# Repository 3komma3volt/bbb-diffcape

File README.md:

# bbb-diffcape

A simple Beaglebone black cape for controlling LED pixels with differential signals

# Usage
It consists of a simple cape with 8 diffential (RS422) outputs to control pixel strings (e.g. with WS2812B LEDs) over long distances. 
The project includes a receiver board to generate single-ended data for the pixels
It is compatible with [FPP Falcon Player](https://github.com/FalconChristmas/fpp) 
The manufacturing files include LCSC component numbers for direct ordering at [JLCPCB](https://jlcpcb.com)
Only the direct-solder fuse, the headers and the screw terminals have to be soldered manually, if ordered at JLCPCB.

> The boards have very simple designs. 2 layer, no impedance matching, only a bit ESD protection, no supply protection!

## Sending Cape

The folder **bbb-diffcape** contains the [KICAD](https://www.kicad.org) schematic, board and Gerber files. 

> Be aware that the Gerbers and board file are not consistent! In the  Gerbers, the screw terminals are a bit too narrow to each other. It works, but the plugged in connectors have to be bend a bit. The KICAD board is already corrected in R2.

 -  A 0.96" I2C OLED TFT can be mounted, which is supported by FPP to get some status information.
 - 5V connector supplies the Beaglebone and the Diffcape
 - Copy the BBB-Diff.json to the */opt/fpp/capes/bbb/strings* folder for correct configuration within FPP

# bbb-diffcape

A simple Beaglebone black cape for controlling LED pixels with differential signals

# Usage
It consists of a simple cape with 8 diffential (RS422) outputs to control pixel strings (e.g. with WS2812B LEDs) over long distances. 
The project includes a receiver board to generate single-ended data for the pixels
It is compatible with [FPP Falcon Player](https://github.com/FalconChristmas/fpp) 
The manufacturing files include LCSC component numbers for direct ordering at [JLCPCB](https://jlcpcb.com)
Only the direct-solder fuse, the headers and the screw terminals have to be soldered manually, if ordered at JLCPCB.

> The boards have very simple designs. 2 layer, no impedance matching, only a bit ESD protection, no supply protection!

## Sending Cape

The folder **bbb-diffcape** contains the [KICAD](https://www.kicad.org) schematic, board and Gerber files. 

> Be aware that the Gerbers and board file are not consistent! In the  Gerbers, the screw terminals are a bit too narrow to each other. It works, but the plugged in connectors have to be bend a bit. The KICAD board is already corrected in R2.

 -  A 0.96" I2C OLED TFT can be mounted, which is supported by FPP to get some status information.
 - 5V connector supplies the Beaglebone and the Diffcape
 - Copy the BBB-Diff.json to the */opt/fpp/capes/bbb/strings* folder for correct configuration within FPP

> This board is tested and fully functional on all channels!

## Receiver

The receiver is designed to support two supply variants

 - Supply with 5V: Just connect power and data as in the picture and the pixel string
 - Supply with 24V via RJ45: For easier cableing, a RJ45 connector for data and power. So there has to be a 24V power supply on the transmission side which powers the system. On the receiver side, a DC/DC converter is needed to power down to 5V. 
 - Excellent for per-prop-use. So one receiver per prop can be used with simple RJ45 cabelling (22AWG) with ~25W supply @ 10m without a big voltage drop
 - Folder "mechanical" contains a FreeCAD file for a simple hotglue mount
 
Because there is no voltage regulator, the receiver is not suited for use with 12V pixels without modifications!

> This board is tested and fully functional!

## ReceiverTransmitter

Receiver with integrated transmitter. With this PCB, you can go back from the last pixel's output to the board and regenerate differential data. It also forwards the 24V power via the RJ45 connector.

> This board is tested and fully functional!

## Distributor

With the distributor power and data can be transfered with standard patch cords. A 3A 5V DC/DC converter is used to supply the beaglebone black

> This board is untested!

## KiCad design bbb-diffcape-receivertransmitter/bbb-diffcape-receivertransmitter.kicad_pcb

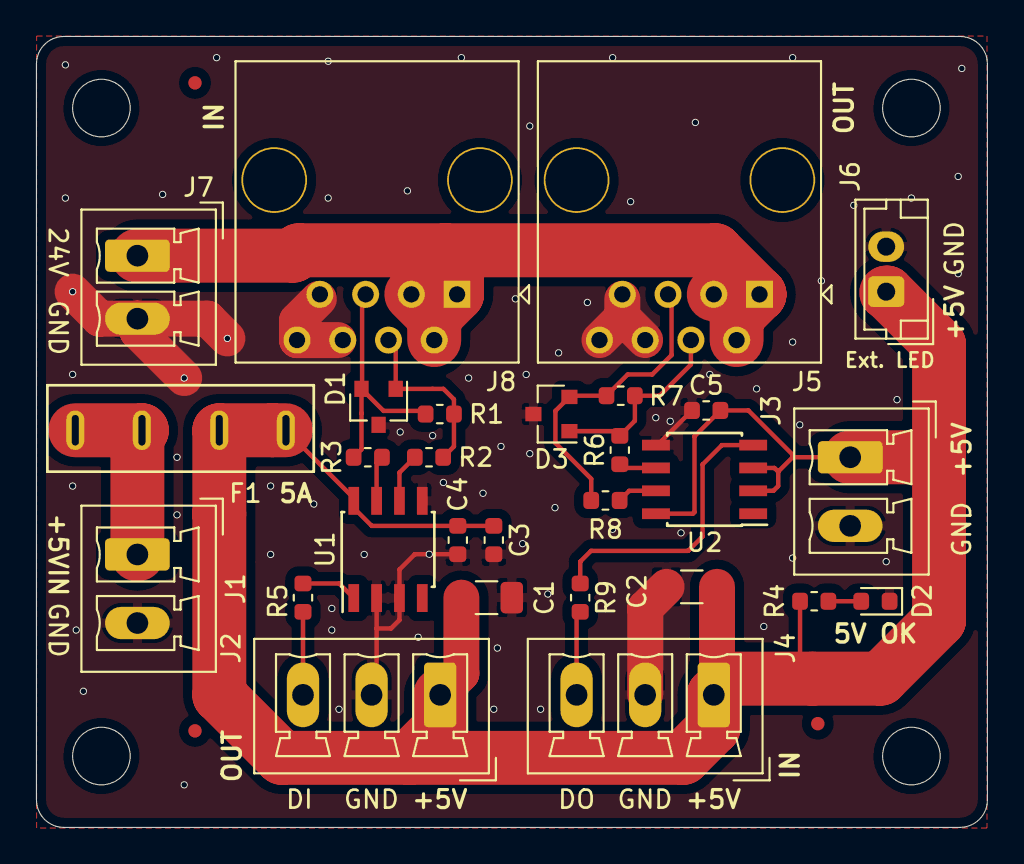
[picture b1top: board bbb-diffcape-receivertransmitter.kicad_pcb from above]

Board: 2 copper layers, 52.8 x 43.9 mm, 35 parts (0 on the bottom side), 17 nets.

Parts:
C1, C2: 100u; C_1206_3216Metric
C3, C4, C5: 100n; C_0603_1608Metric
D1, D3: PSM712; SOT-23
D2: LED; LED_0603_1608Metric
F1: 5A; TLZWLA-Minifuse
FID1, FID2, FID3: Fiducial; Fiducial_0.75mm_Mask1.5mm
H1, H2, H3, H4: MountingHole; MountingHole_3.2mm_M3
J1, J3: Screw_Terminal_01x02; PhoenixContact_MCV_1,5_2-G-3.81_1x02_P3.81mm_Vertical
J2, J4: Screw_Terminal_01x03; PhoenixContact_MCV_1,5_3-G-3.81_1x03_P3.81mm_Vertical
J5, J8: RJ45; RJ45_OST_PJ012-8P8CX_Vertical
J6: Conn_01x02_Male; JST_EH_B2B-EH-A_1x02_P2.50mm_Vertical
J7: Screw_Terminal_01x02; PhoenixContact_MCV_1,5_2-G-3.5_1x02_P3.50mm_Vertical
R1, R7: 120; R_0603_1608Metric
R2, R3, R5, R6, R8, R9: 10; R_0603_1608Metric
R4: 470; R_0603_1608Metric
U1, U2: SP3485EN; SOIC-8_3.9x4.9mm_P1.27mm

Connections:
+5V: C1.1, C2.1, C3.1, C4.1, C5.1, F1.1, J2.1, J3.1, J4.1, J6.1, R4.2, U1.8, U2.2, U2.3, U2.8
+24V: J5.1, J5.2, J5.3, J7.1, J8.1, J8.2, J8.3
/DataIn: J4.3, R9.2
/PW_In: F1.2, J1.1
/RS422_A: D1.1, J8.4, R1.1, R2.1
/RS422_A_Out: D3.1, J5.4, R6.1, R7.1
/RS422_B: D1.2, J8.5, R1.2, R3.1
/RS422_B_Out: D3.2, J5.5, R7.2, R8.1
GNDD: C1.2, C2.2, C3.2, C4.2, C5.2, D1.3, D2.1, D3.3, J1.2, J2.2, J3.2, J4.2, J5.6, J5.7, J5.8, J6.2, J7.2, J8.6, J8.7, J8.8, U1.2, U1.3, U1.5, U2.5
unnamed: D2.2, R4.1
unnamed: J2.3, R5.2
unnamed: R2.2, U1.6
unnamed: R3.2, U1.7
unnamed: R5.1, U1.1
unnamed: R6.2, U2.6
unnamed: R8.2, U2.7
unnamed: R9.1, U2.4

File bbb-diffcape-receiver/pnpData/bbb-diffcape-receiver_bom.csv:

Comment,Designator,Footprint,LCSC
"100u","C1,C2","Capacitor_SMD:C_1206_3216Metric","C15008"
"100n","C3,C4","Capacitor_SMD:C_0603_1608Metric","C14663"
"PSM712","D1","Package_TO_SOT_SMD:SOT-23","C32677"
"LED","D2","LED_SMD:LED_0603_1608Metric","C72038"
"5A","F1","Fuse:Fuse_Blade_Mini_directSolder",""
"Fiducial","FID1,FID2,FID3","Fiducial:Fiducial_0.75mm_Mask1.5mm",""
"MountingHole","H1,H2,H3,H4","MountingHole:MountingHole_3.2mm_M3",""
"Screw_Terminal_01x03","J2,J5","Connector_Phoenix_MC:PhoenixContact_MCV_1,5_3-G-3.5_1x03_P3.50mm_Vertical",""
"Screw_Terminal_01x02","J1,J3,J4,J7","Connector_Phoenix_MC:PhoenixContact_MCV_1,5_2-G-3.5_1x02_P3.50mm_Vertical",""
"Conn_01x02_Male","J6","Connector_JST:JST_EH_B2B-EH-A_1x02_P2.50mm_Vertical",""
"RJ45","J8","Connector_RJ:RJ45_OST_PJ012-8P8CX_Vertical",""
"120","R1","Resistor_SMD:R_0603_1608Metric","C22787"
"10","R2,R3,R5","Resistor_SMD:R_0603_1608Metric","C22859"
"470","R4","Resistor_SMD:R_0603_1608Metric","C23182"
"SP3485EN","U1","Package_SO:SOIC-8_3.9x4.9mm_P1.27mm",""

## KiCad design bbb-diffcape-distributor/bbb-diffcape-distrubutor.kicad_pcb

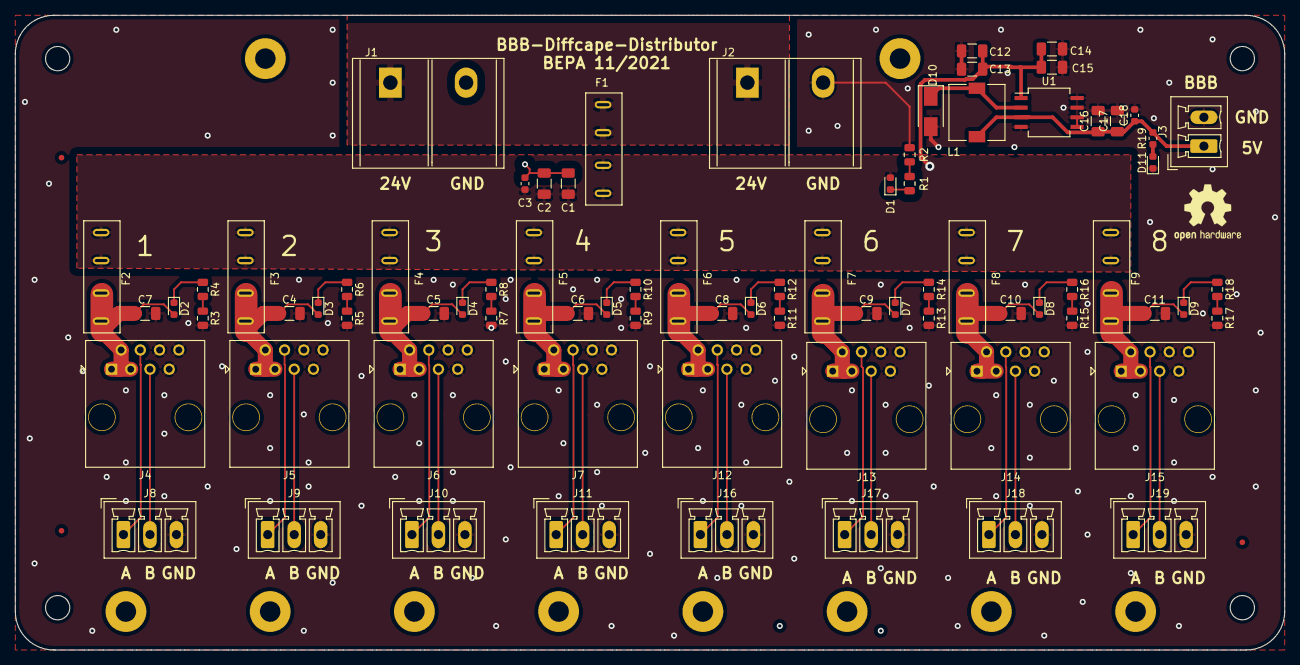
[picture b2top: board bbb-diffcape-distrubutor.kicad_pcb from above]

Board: 2 copper layers, 167.6 x 83.8 mm, 85 parts (0 on the bottom side), 48 nets.

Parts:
C1, C2, C4, C5, C6, C7, C8, C9, C10, C11, C12, C13, C14, C15, C16, C17: 100u; C_1206_3216Metric
C3, C18: 100n; C_0603_1608Metric
D1, D2, D3, D4, D5, D6, D7, D8, D9, D11: LED; LED_0603_1608Metric
D10: SS54; D_SMA
F1: 20A; TLZWLA-Minifuse
F2, F3, F4, F5, F6, F7, F8, F9: 2A; TLZWLA-Minifuse
FID1, FID2, FID3: Fiducial; Fiducial_0.75mm_Mask1.5mm
H1, H2, H3, H4: MountingHole; MountingHole_3.2mm_M3
J1, J2: Screw_Terminal_01x02; KF1000-2P
J3: Screw_Terminal_01x02; PhoenixContact_MCV_1,5_2-G-3.81_1x02_P3.81mm_Vertical
J4, J5, J6, J7, J12, J13, J14, J15: RJ45; RJ45_OST_PJ012-8P8CX_Vertical
J8, J9, J10, J11, J16, J17, J18, J19: Screw_Terminal_01x03; PhoenixContact_MCV_1,5_3-G-3.5_1x03_P3.50mm_Vertical
L1: 68uH; L_7.3x7.3_H3.5
R1, R2, R3, R4, R5, R6, R7, R8, R9, R10, R11, R12, R13, R14, R15, R16, R17, R18: 1k2; R_0805_2012Metric
R19: 470; R_0603_1608Metric
U1: XL1509-5.0E1; SO-8_5.3x6.2mm_P1.27mm

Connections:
+5V: C16.1, C17.1, C18.1, J3.1, L1.2, R19.2, U1.3
+24V: C1.1, C2.1, C3.1, C12.1, C13.1, C14.1, C15.1, D1.2, F1.1, F2.2, F3.2, F4.2, F5.2, F6.2, F7.2, F8.2, F9.2, U1.1
/PW_In: F1.2, J1.1, J2.1
GNDD: C1.2, C2.2, C3.2, C4.2, C5.2, C6.2, C7.2, C8.2, C9.2, C10.2, C11.2, C12.2, C13.2, C14.2, C15.2, C16.2, C17.2, C18.2, D10.2, D11.1, J1.2, J2.2, J3.2, J4.6, J4.7, J4.8, J5.6, J5.7, J5.8, J6.6, J6.7, J6.8, J7.6, J7.7, J7.8, J8.3, J9.3, J10.3, J11.3, J12.6, J12.7, J12.8, J13.6, J13.7, J13.8, J14.6, J14.7, J14.8, J15.6, J15.7, J15.8, J16.3, J17.3, J18.3, J19.3, R2.2, R3.2, R5.2, R7.2, R9.2, R11.2, R13.2, R15.2, R17.2, U1.4, U1.5, U1.6, U1.7, U1.8
unnamed: C4.1, D3.2, F3.1, J5.1, J5.2, J5.3
unnamed: C5.1, D4.2, F4.1, J6.1, J6.2, J6.3
unnamed: C6.1, D5.2, F5.1, J7.1, J7.2, J7.3
unnamed: C7.1, D2.2, F2.1, J4.1, J4.2, J4.3
unnamed: C8.1, D6.2, F6.1, J12.1, J12.2, J12.3
unnamed: C9.1, D7.2, F7.1, J13.1, J13.2, J13.3
unnamed: C10.1, D8.2, F8.1, J14.1, J14.2, J14.3
unnamed: C11.1, D9.2, F9.1, J15.1, J15.2, J15.3
unnamed: D1.1, R1.1
unnamed: D2.1, R4.1
unnamed: D3.1, R6.1
unnamed: D4.1, R8.1
unnamed: D5.1, R10.1
unnamed: D6.1, R12.1
unnamed: D7.1, R14.1
unnamed: D8.1, R16.1
unnamed: D9.1, R18.1
unnamed: D10.1, L1.1, U1.2
unnamed: D11.2, R19.1
unnamed: J4.4, J8.1
unnamed: J4.5, J8.2
unnamed: J5.4, J9.1
unnamed: J5.5, J9.2
unnamed: J6.4, J10.1
unnamed: J6.5, J10.2
unnamed: J7.4, J11.1
unnamed: J7.5, J11.2
unnamed: J12.4, J16.1
unnamed: J12.5, J16.2
unnamed: J13.4, J17.1
unnamed: J13.5, J17.2
unnamed: J14.4, J18.1
unnamed: J14.5, J18.2
unnamed: J15.4, J19.1
unnamed: J15.5, J19.2
unnamed: R1.2, R2.1
unnamed: R3.1, R4.2
unnamed: R5.1, R6.2
unnamed: R7.1, R8.2
unnamed: R9.1, R10.2
unnamed: R11.1, R12.2
unnamed: R13.1, R14.2
unnamed: R15.1, R16.2
unnamed: R17.1, R18.2

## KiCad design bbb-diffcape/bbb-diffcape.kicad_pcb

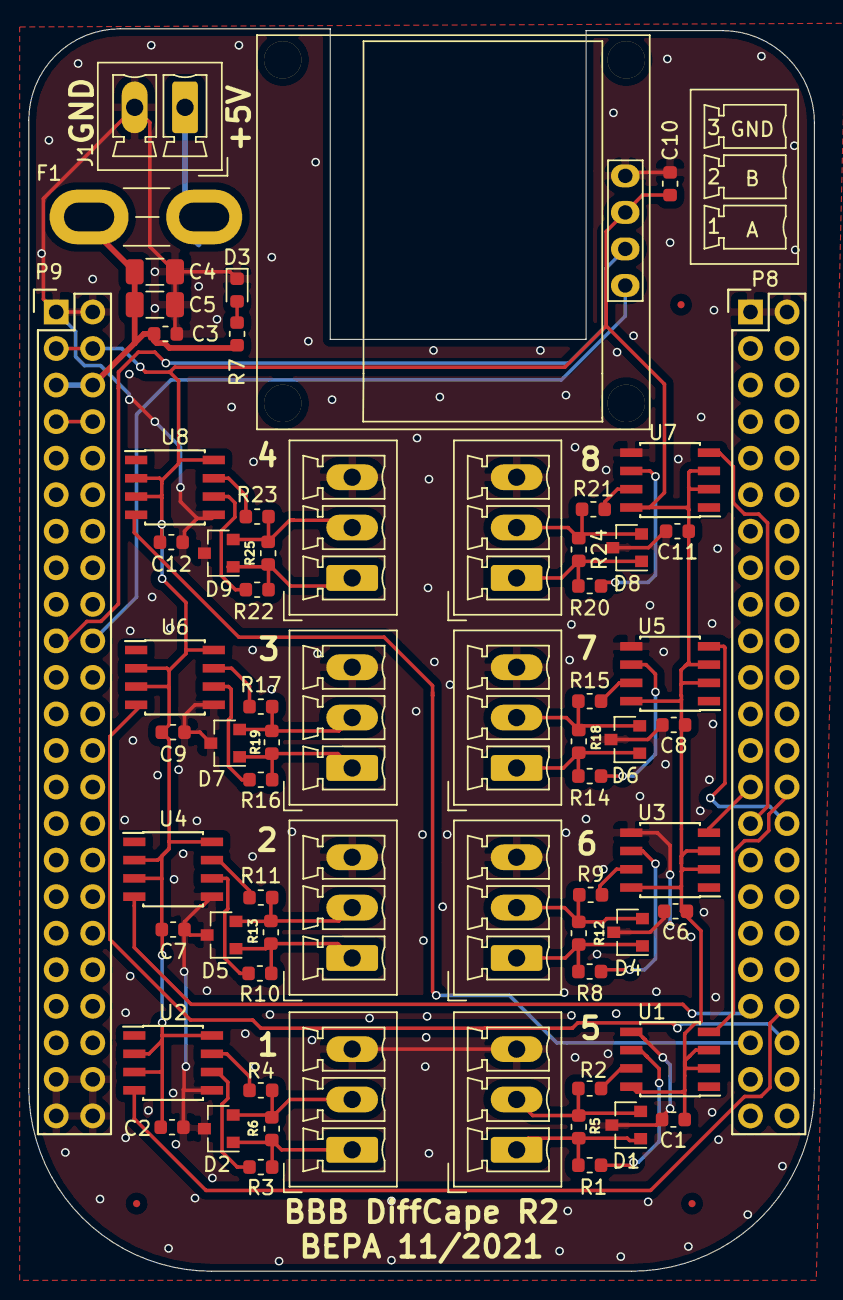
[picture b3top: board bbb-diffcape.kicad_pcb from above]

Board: 2 copper layers, 54.6 x 86.4 mm, 70 parts (0 on the bottom side), 48 nets.

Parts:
Brd1: SSD1306; 128x64OLED
C1, C2, C3, C6, C7, C8, C9, C10, C11, C12: 100n; C_0603_1608Metric
C4, C5: 100u; C_1206_3216Metric
D1, D2, D4, D5, D6, D7, D8, D9: PSM712; SOT-23
D3: LED; LED_0603_1608Metric
F1: 2A; Fuse_Blade_Mini_directSolder
FID1, FID2, FID3: Fiducial; Fiducial_0.5mm_Mask1mm
J1: Screw_Terminal_01x02; PhoenixContact_MCV_1,5_2-G-3.5_1x02_P3.50mm_Vertical
J2, J3, J4, J5, J6, J7, J8, J9: Screw_Terminal_01x03; PhoenixContact_MCV_1,5_3-G-3.5_1x03_P3.50mm_Vertical
P8, P9: BeagleBone_Black_Header; Socket_BeagleBone_Black
R1, R2, R3, R4, R8, R9, R10, R11, R14, R15, R16, R17, R20, R21, R22, R23: 10; R_0603_1608Metric
R5, R6, R12, R13, R18, R19, R24, R25: 120; R_0603_1608Metric
R7: 470; R_0603_1608Metric
U1, U2, U3, U4, U5, U6, U7, U8: SP3485EN; SOIC-8_3.9x4.9mm_P1.27mm

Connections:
+3V3: Brd1.2, C1.1, C2.1, C6.1, C7.1, C8.1, C9.1, C10.1, C11.1, C12.1, P9.3, P9.4, U1.2, U1.3, U1.8, U2.2, U2.3, U2.8, U3.2, U3.3, U3.8, U4.2, U4.3, U4.8, U5.2, U5.3, U5.8, U6.2, U6.3, U6.8, U7.2, U7.3, U7.8, U8.2, U8.3, U8.8
+5V: C3.1, C4.1, C5.1, F1.1, P9.5, P9.6, R7.1
/5Vin: F1.2, J1.1
GNDD: Brd1.1, C1.2, C2.2, C3.2, C4.2, C5.2, C6.2, C7.2, C8.2, C9.2, C10.2, C11.2, C12.2, D1.3, D2.3, D3.1, D4.3, D5.3, D6.3, D7.3, D8.3, D9.3, J1.2, J2.3, J3.3, J4.3, J5.3, J6.3, J7.3, J8.3, J9.3, P8.1, P8.2, P9.1, P9.2, P9.43, P9.44, P9.45, P9.46, U1.5, U2.5, U3.5, U4.5, U5.5, U6.5, U7.5, U8.5
unnamed: D1.1, J2.1, R1.1, R5.2
unnamed: D1.2, J2.2, R2.1, R5.1
unnamed: D2.1, J3.1, R3.1, R6.2
unnamed: D2.2, J3.2, R4.1, R6.1
unnamed: D3.2, R7.2
unnamed: D4.1, J4.1, R8.1, R12.2
unnamed: D4.2, J4.2, R9.1, R12.1
unnamed: D5.1, J5.1, R10.1, R13.2
unnamed: D5.2, J5.2, R11.1, R13.1
unnamed: D6.1, J6.1, R14.1, R18.2
unnamed: D6.2, J6.2, R15.1, R18.1
unnamed: D7.1, J7.1, R16.1, R19.2
unnamed: D7.2, J7.2, R17.1, R19.1
unnamed: D8.1, J8.1, R20.1, R24.2
unnamed: D8.2, J8.2, R21.1, R24.1
unnamed: D9.1, J9.1, R22.1, R25.2
unnamed: D9.2, J9.2, R23.1, R25.1
unnamed: R1.2, U1.6
unnamed: R2.2, U1.7
unnamed: R3.2, U2.6
unnamed: R4.2, U2.7
unnamed: R8.2, U3.6
unnamed: R9.2, U3.7
unnamed: R10.2, U4.6
unnamed: R11.2, U4.7
unnamed: R14.2, U5.6
unnamed: R15.2, U5.7
unnamed: R16.2, U6.6
unnamed: R17.2, U6.7
unnamed: R20.2, U7.6
unnamed: R21.2, U7.7
unnamed: R22.2, U8.6
unnamed: R23.2, U8.7
OLED_SCL: Brd1.3, P9.19
OLED_SDA: Brd1.4, P9.20
SYS_5V: P9.7, P9.8
String1: P8.28, U1.4
String2: P8.27, U3.4
String3: P8.30, U5.4
String4: P8.29, U7.4
String5: P8.40, U2.4
String6: P8.39, U4.4
String7: P8.42, U6.4
String8: P8.41, U8.4

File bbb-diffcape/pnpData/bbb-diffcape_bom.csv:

Comment,Designator,Footprint,LCSC
"SSD1306","Brd1","oled:128x64OLED",""
"100n","C1,C2,C3,C6,C7,C8,C9,C10,C11,C12","Capacitor_SMD:C_0603_1608Metric","C14663"
"100u","C4,C5","Capacitor_SMD:C_1206_3216Metric","C15008"
"PSM712","D1,D2,D4,D5,D6,D7,D8,D9","Package_TO_SOT_SMD:SOT-23","C32677"
"LED","D3","LED_SMD:LED_0603_1608Metric","C72038"
"2A","F1","Fuse:Fuse_Blade_Mini_directSolder",""
"Fiducial","FID1,FID2,FID3","Fiducial:Fiducial_0.5mm_Mask1mm",""
"Screw_Terminal_01x02","J1","Connector_Phoenix_MC:PhoenixContact_MCV_1,5_2-G-3.5_1x02_P3.50mm_Vertical",""
"Screw_Terminal_01x03","J2,J3,J4,J5,J6,J7,J8,J9","Connector_Phoenix_MC:PhoenixContact_MCV_1,5_3-G-3.5_1x03_P3.50mm_Vertical",""
"BeagleBone_Black_Header","P8,P9","Socket_BeagleBone_Black:Socket_BeagleBone_Black",""
"10","R1,R2,R3,R4,R8,R9,R10,R11,R14,R15,R16,R17,R20,R21,R22,R23","Resistor_SMD:R_0603_1608Metric","C22859"
"120","R5,R6,R12,R13,R18,R19,R24,R25","Resistor_SMD:R_0603_1608Metric","C22787"
"470","R7","Resistor_SMD:R_0603_1608Metric","C23182"
"SP3485EN","U1,U2,U3,U4,U5,U6,U7,U8","Package_SO:SOIC-8_3.9x4.9mm_P1.27mm","C8963"

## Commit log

2021-11-07 Add files via upload
    Initial commit
2021-11-17 Added distributor
    Added schematic and board for distributor
2021-11-17 Corrected folders, added some documentation in readme
2021-12-10 Added new receiver/transmitter PCB
2021-12-24 Corrected Input and Output labeling on silkscreen
2021-12-26 Update README.md
    Corrected readme
